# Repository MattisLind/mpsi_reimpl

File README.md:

# MPSI Rev2

A new HP 9830 interface based on
[Brent Hilpert's MPSI](https://madrona.ca/e/HP9830/mpsi/index.html): a 5 V ATF1504AS
CPLD handles the bus, and an STM32F103CB serves files from a microSD card.
Two 74HCT165s capture input, separate SPI buses serve the HP link and SD,
and an SSD1306 OLED with up/down/select buttons controls operation.

MPSI Server handles paper tape, printer capture and Fast Mode cassette emulation.
Tape Controller uses an HP-resident MTAPE proxy to read/write the physical drive.
USB MSC takes exclusive ownership of SD and releases every HP output.
See [the tape analysis](requirements/07_tape_analysis.md).

The current draft includes:

- [VHDL RTL, handshake bench and container build flow](hardware/rev2/README.md).
- [STM32/CPLD package pins and tentative placement](requirements/08_pin_mapping.md).
- [Three-sheet KiCad schematic and unrouted placement](hardware/rev2/kicad/README.md),
  with the existing HP connector, USB-C protection and PA9/PA10 debug header.
- [Portable C firmware core](firmware/rev2/README.md).

Start with [requirements](requirements/README.md) and [open issues](open_issues.md).

```sh
make test
```

Requires make, a C11 compiler and either GHDL or the documented Docker image.
Tests cover bus handshakes, five interrupt choices, GP-only Controller decoding,
direct configuration updates, unbuffered data, CS-clocked flags, input capture, tape commands
and exclusive SD/MSC ownership.

The simplified ATF1504 design fits and generates JEDEC with all 29 requested pins,
JTAG and fourteen open-collector HP outputs. RTL and fitter-emitted functional
equations each pass 2,000 checks at 9, 18 and 24 MHz SPI. These are zero-delay
tests; the F103 is specified up to 18 MHz, and 9 MHz is the provisional board rate.
This remains a design draft. Timing, fitter-report accounting, electrical current/rail and power-up validation, PCB routing,
and Arduino SD/USB/UI/Controller drivers also remain open. The STM32 pin map uses
PB14/PB10 as direct 5 V tolerant inputs, subject to supply/reset constraints.

Previous files remain in `MPSIBOARD`, `hardware/pld` and `software`.
The original README is preserved in [docs/legacy_design.md](docs/legacy_design.md).

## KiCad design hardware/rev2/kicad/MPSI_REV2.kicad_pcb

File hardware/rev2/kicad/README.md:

# KiCad draft

Open [MPSI_REV2.kicad_pro](MPSI_REV2.kicad_pro) in KiCad 10.

The root sheet contains the copied HP connector, ATF1504AS-10JU44, two 74HCT165s,
JTAG and reset/control pulls. The MCU sheet contains STM32F103CBT6, microSD with
card detection, OLED/buttons, USART1 debug, SWD, boot jumper and 8 MHz crystal.
The USB/power sheet copies the paper-tape project's USB-C/USBLC6 circuit and
Schottky source isolation, with TLV75533 3.3 V regulation.

The 64-footprint board is an **unrouted placement draft**. Its HP connector and
Edge.Cuts use the current legacy board. All fifty connector pad positions,
sizes, angles and layers are checked against that board when regenerated.
The CPLD and HCT165s sit beside the HP edge connector; MCU is to their right,
with SD/UI/debug/USB towards the other edges. Mechanical fit and routing remain
to be reviewed. The simplified CPLD fits with the requested package pins, including
CS moved to GCLK3 pin 41. COMMIT/overrun wiring is removed; PB0/PB11 and CPLD
34/39/40 are spare. Electrical/timing validation and routing remain open.

The project embeds symbols and supplies portable `Rev2.kicad_sym` and
`Rev2.pretty` libraries. The connector library is extracted from
`MPSIBOARD/MPSIBOARD.kicad_pcb`; board-file pad angles are normalized to library
angles without changing pad geometry. USB-C symbol/footprint and circuit values
come from [the paper-tape project](https://github.com/MattisLind/hp21xx_papertape_emulator/tree/06787ada3dd411305c0451a057edc152249f1b82/kicad/hp21xx_papertape_emulator).
Original projects are untouched.

The schematic generator uses installed KiCad symbol libraries and local copies
of that reference schematic/PCB. Its `--reference`, `--reference-pcb` and
`--symbols` arguments allow overriding the defaults. The saved KiCad project
does not depend on those source files being installed.

```sh
python3 scripts/generate_rev2_schematic.py
kicad-cli sch export netlist --output /tmp/mpsi-rev2.net hardware/rev2/kicad/MPSI_REV2.kicad_sch
python3 scripts/check_rev2_pins.py --netlist /tmp/mpsi-rev2.net
```

For the placement generator use KiCad's bundled Python with its `pcbnew` module;
it consumes the above netlist, including explicit unconnected pin nets. On macOS:

```sh
/Applications/KiCad/KiCad.app/Contents/Frameworks/Python.framework/Versions/3.9/bin/python3.9 scripts/generate_rev2_placement.py
```

`components.json` records the schematic components/UUID paths used by that
generator; `pinmap.json` in the parent directory is the package-pin contract.
Generators overwrite these draft files, so update generator source alongside
manual schematic changes if regeneration is needed.

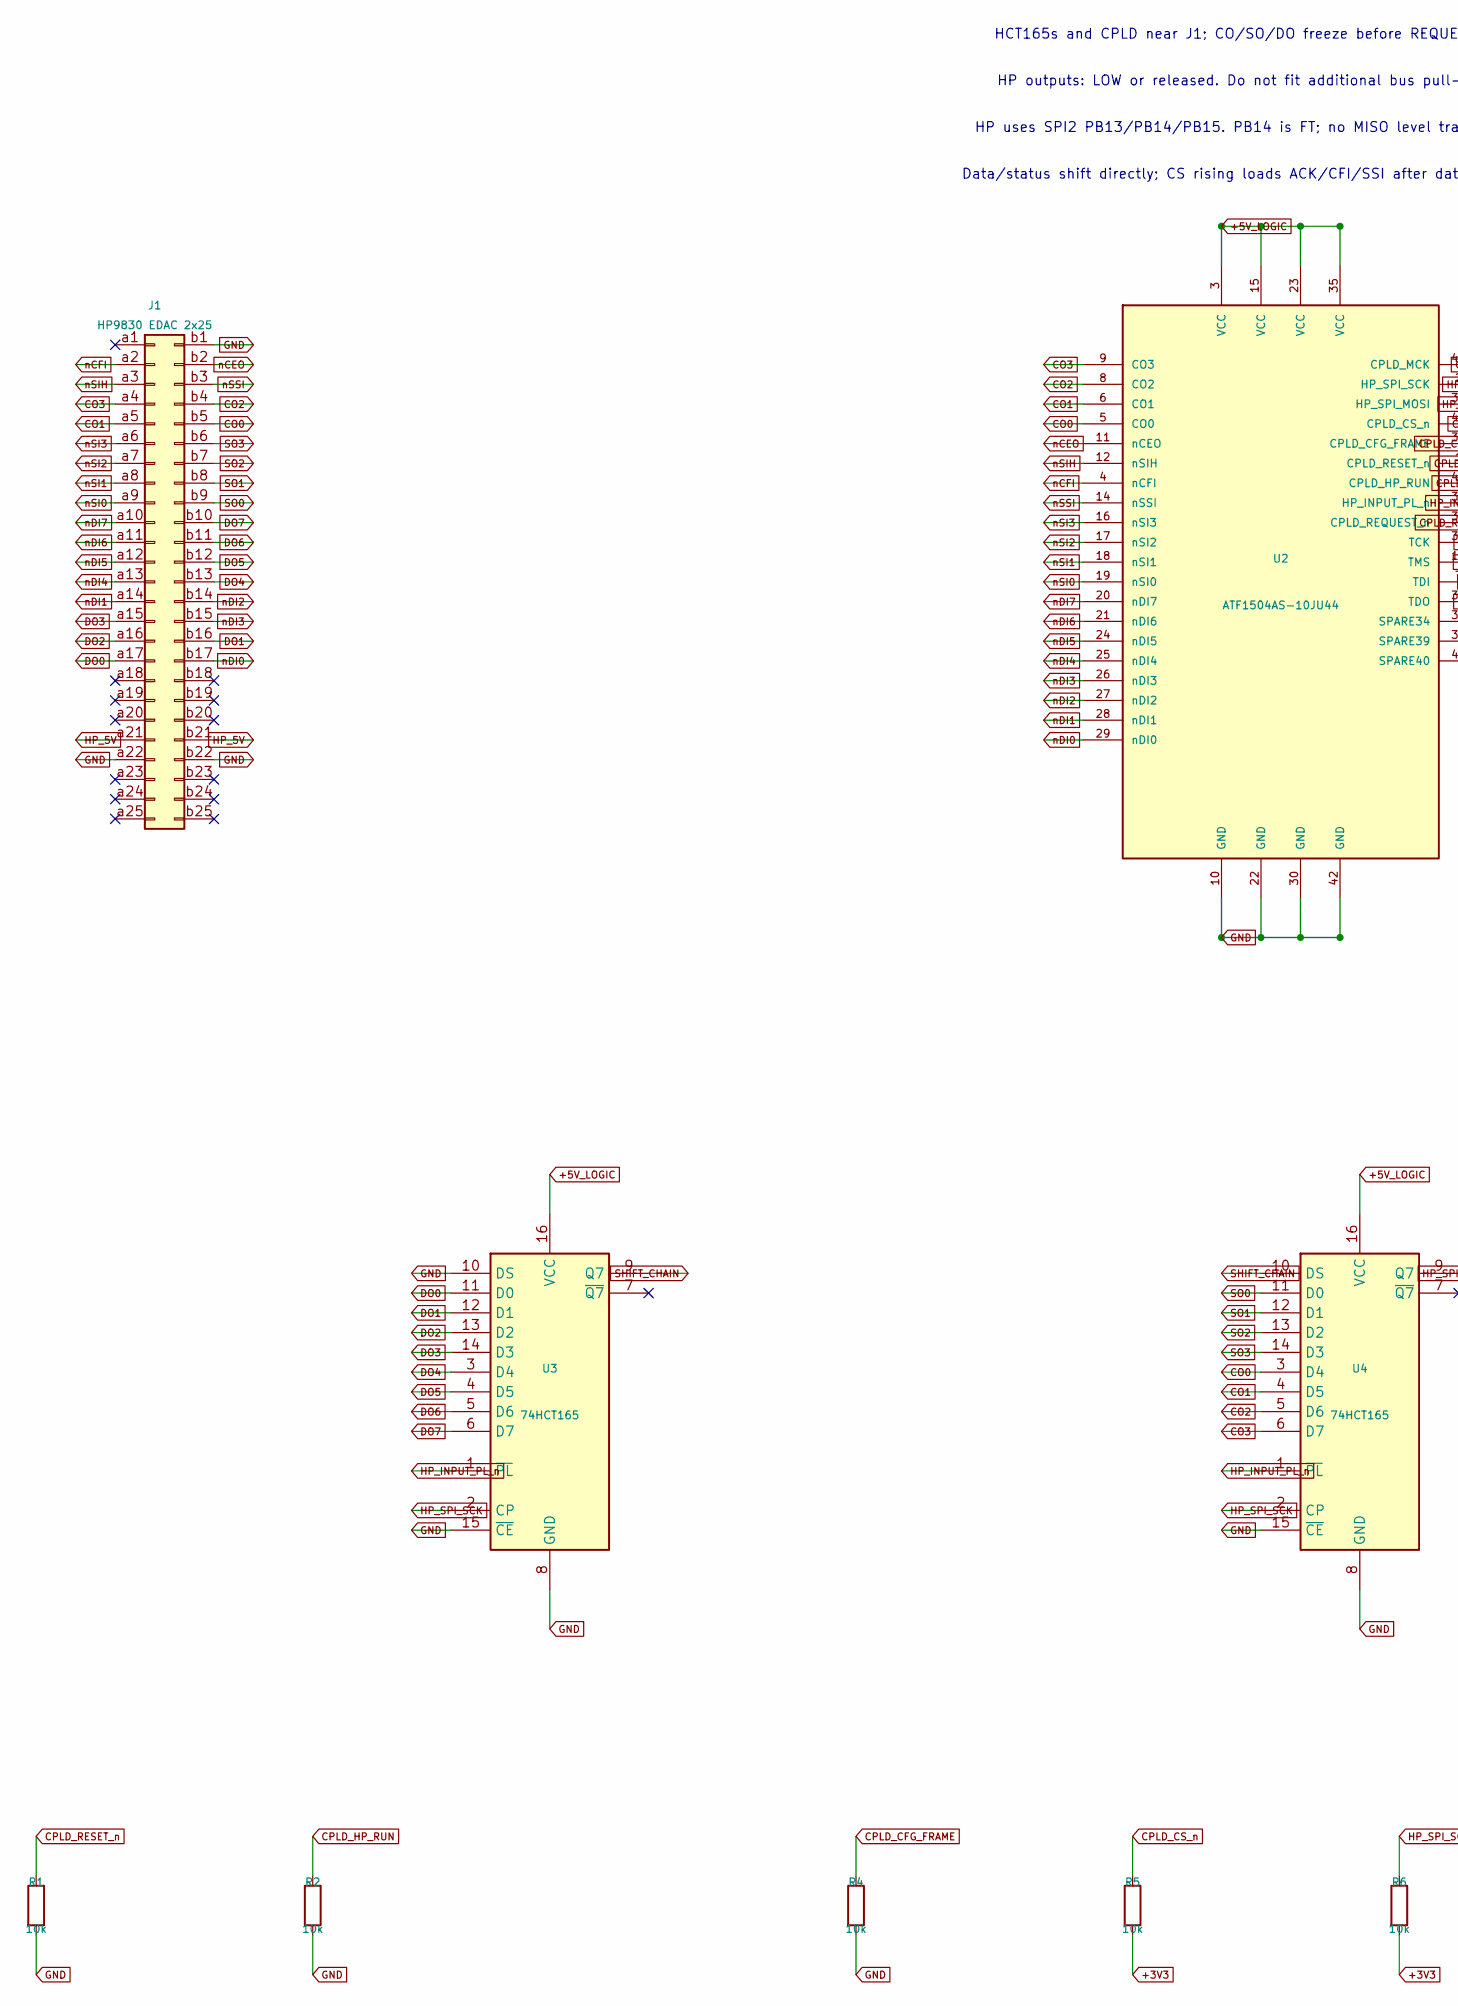
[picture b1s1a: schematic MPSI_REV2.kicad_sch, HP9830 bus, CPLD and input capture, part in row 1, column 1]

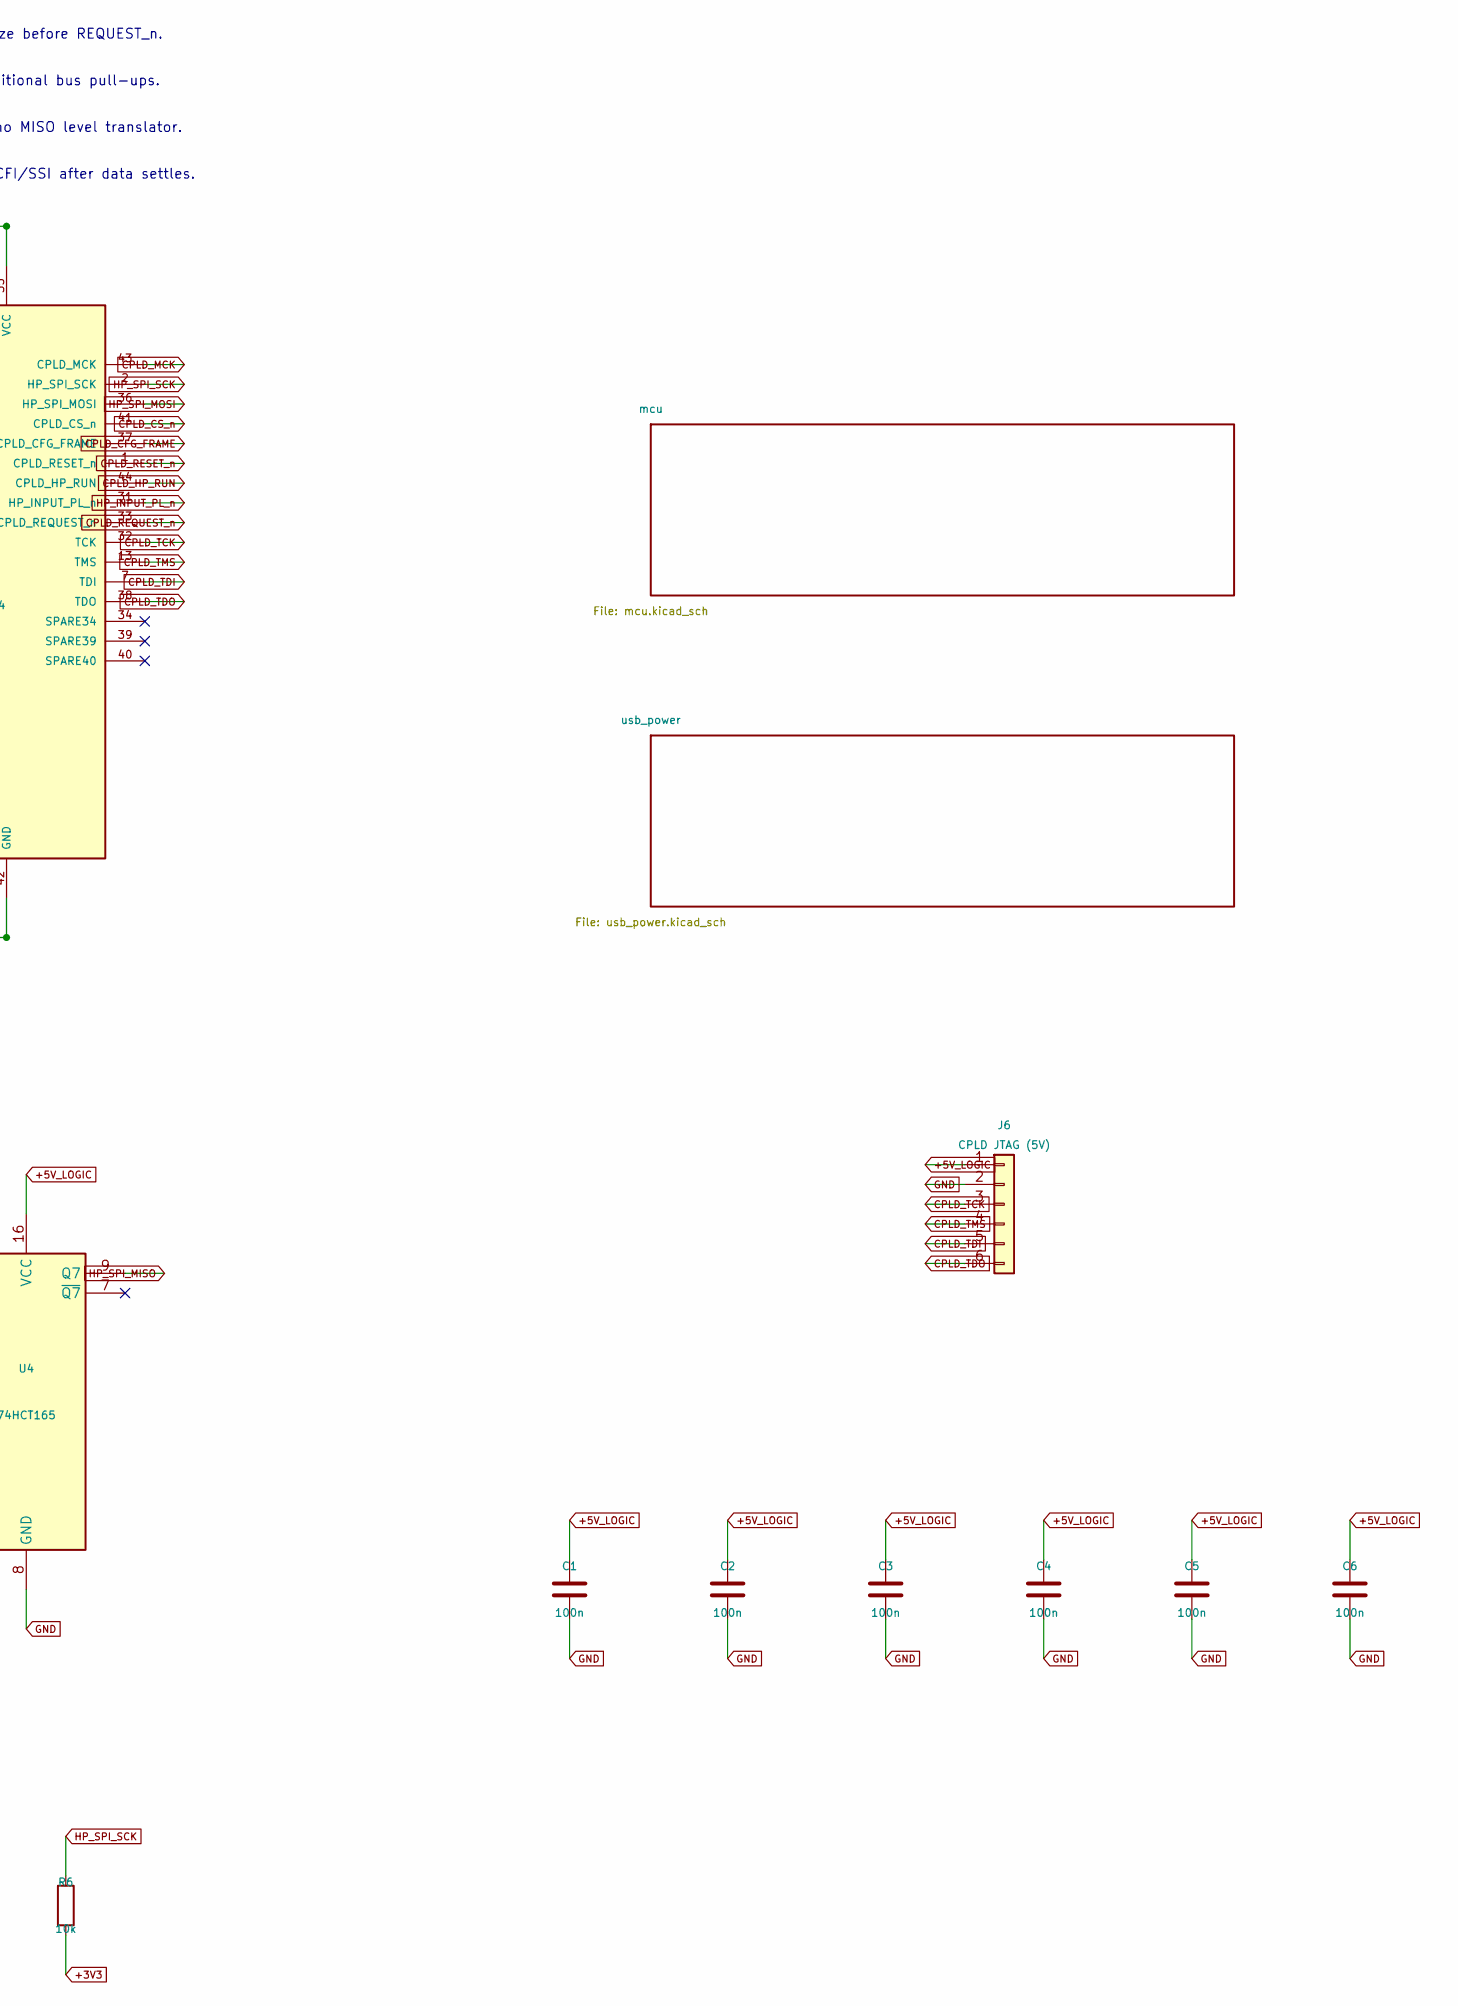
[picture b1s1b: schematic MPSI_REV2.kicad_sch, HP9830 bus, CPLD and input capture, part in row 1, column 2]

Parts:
C1, C2, C3, C4, C5, C6: 100n; C_0603_1608Metric
J1: HP9830 EDAC 2x25; HP9830_EDAC_2x25
J6: CPLD JTAG (5V); PinHeader_1x06_P2.54mm_Vertical
R1, R2, R4, R5, R6: 10k; R_0603_1608Metric
U2: ATF1504AS-10JU44; PLCC-44_16.6x16.6mm_P1.27mm
U3, U4: 74HCT165; SOIC-16_3.9x9.9mm_P1.27mm

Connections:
+3V3: R5.2, R6.2; also elsewhere on the board
+5V_LOGIC: C1.1, C2.1, C3.1, C4.1, C5.1, C6.1, J6.1, U2.3 (VCC), U2.15 (VCC), U2.23 (VCC), U2.35 (VCC), U3.16 (VCC), U4.16 (VCC); also elsewhere on the board
CO0: J1.b5, U2.5 (CO0), U4.3 (D4)
CO1: J1.a5, U2.6 (CO1), U4.4 (D5)
CO2: J1.b4, U2.8 (CO2), U4.5 (D6)
CO3: J1.a4, U2.9 (CO3), U4.6 (D7)
CPLD_CFG_FRAME: R4.1, U2.37 (CPLD_CFG_FRAME); also elsewhere on the board
CPLD_CS_n: R5.1, U2.41 (CPLD_CS_n); also elsewhere on the board
CPLD_HP_RUN: R2.1, U2.44 (CPLD_HP_RUN); also elsewhere on the board
CPLD_MCK: U2.43 (CPLD_MCK); also elsewhere on the board
CPLD_REQUEST_n: U2.33 (CPLD_REQUEST_n); also elsewhere on the board
CPLD_RESET_n: R1.1, U2.1 (CPLD_RESET_n); also elsewhere on the board
CPLD_TCK: J6.3, U2.32 (TCK)
CPLD_TDI: J6.5, U2.7 (TDI)
CPLD_TDO: J6.6, U2.38 (TDO)
CPLD_TMS: J6.4, U2.13 (TMS)
DO0: J1.a17, U3.11 (D0)
DO1: J1.b16, U3.12 (D1)
DO2: J1.a16, U3.13 (D2)
DO3: J1.a15, U3.14 (D3)
DO4: J1.b13, U3.3 (D4)
DO5: J1.b12, U3.4 (D5)
DO6: J1.b11, U3.5 (D6)
DO7: J1.b10, U3.6 (D7)
GND: C1.2, C2.2, C3.2, C4.2, C5.2, C6.2, J1.a22, J1.b1, J1.b22, J6.2, R1.2, R2.2, R4.2, U2.10 (GND), U2.22 (GND), U2.30 (GND), U2.42 (GND), U3.8 (GND), U3.10 (DS), U3.15 (~CE), U4.8 (GND), U4.15 (~CE); also elsewhere on the board
HP_5V: J1.a21, J1.b21; also elsewhere on the board
HP_INPUT_PL_n: U2.31 (HP_INPUT_PL_n), U3.1 (~PL), U4.1 (~PL)
HP_SPI_MISO: U4.9 (Q7); also elsewhere on the board
HP_SPI_MOSI: U2.36 (HP_SPI_MOSI); also elsewhere on the board
HP_SPI_SCK: R6.1, U2.2 (HP_SPI_SCK), U3.2 (CP), U4.2 (CP); also elsewhere on the board
SHIFT_CHAIN: U3.9 (Q7), U4.10 (DS)
SO0: J1.b9, U4.11 (D0)
SO1: J1.b8, U4.12 (D1)
SO2: J1.b7, U4.13 (D2)
SO3: J1.b6, U4.14 (D3)
nCEO: J1.b2, U2.11 (nCEO)
nCFI: J1.a2, U2.4 (nCFI)
nDI0: J1.b17, U2.29 (nDI0)
nDI1: J1.a14, U2.28 (nDI1)
nDI2: J1.b14, U2.27 (nDI2)
nDI3: J1.b15, U2.26 (nDI3)
nDI4: J1.a13, U2.25 (nDI4)
nDI5: J1.a12, U2.24 (nDI5)
nDI6: J1.a11, U2.21 (nDI6)
nDI7: J1.a10, U2.20 (nDI7)
nSI0: J1.a9, U2.19 (nSI0)
nSI1: J1.a8, U2.18 (nSI1)
nSI2: J1.a7, U2.17 (nSI2)
nSI3: J1.a6, U2.16 (nSI3)
nSIH: J1.a3, U2.12 (nSIH)
nSSI: J1.b3, U2.14 (nSSI)

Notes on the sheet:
HCT165s and CPLD near J1; CO/SO/DO freeze before REQUEST_n.
HP outputs: LOW or released. Do not fit additional bus pull-ups.
HP uses SPI2 PB13/PB14/PB15. PB14 is FT; no MISO level translator.
Data/status shift directly; CS rising loads ACK/CFI/SSI after data settles.

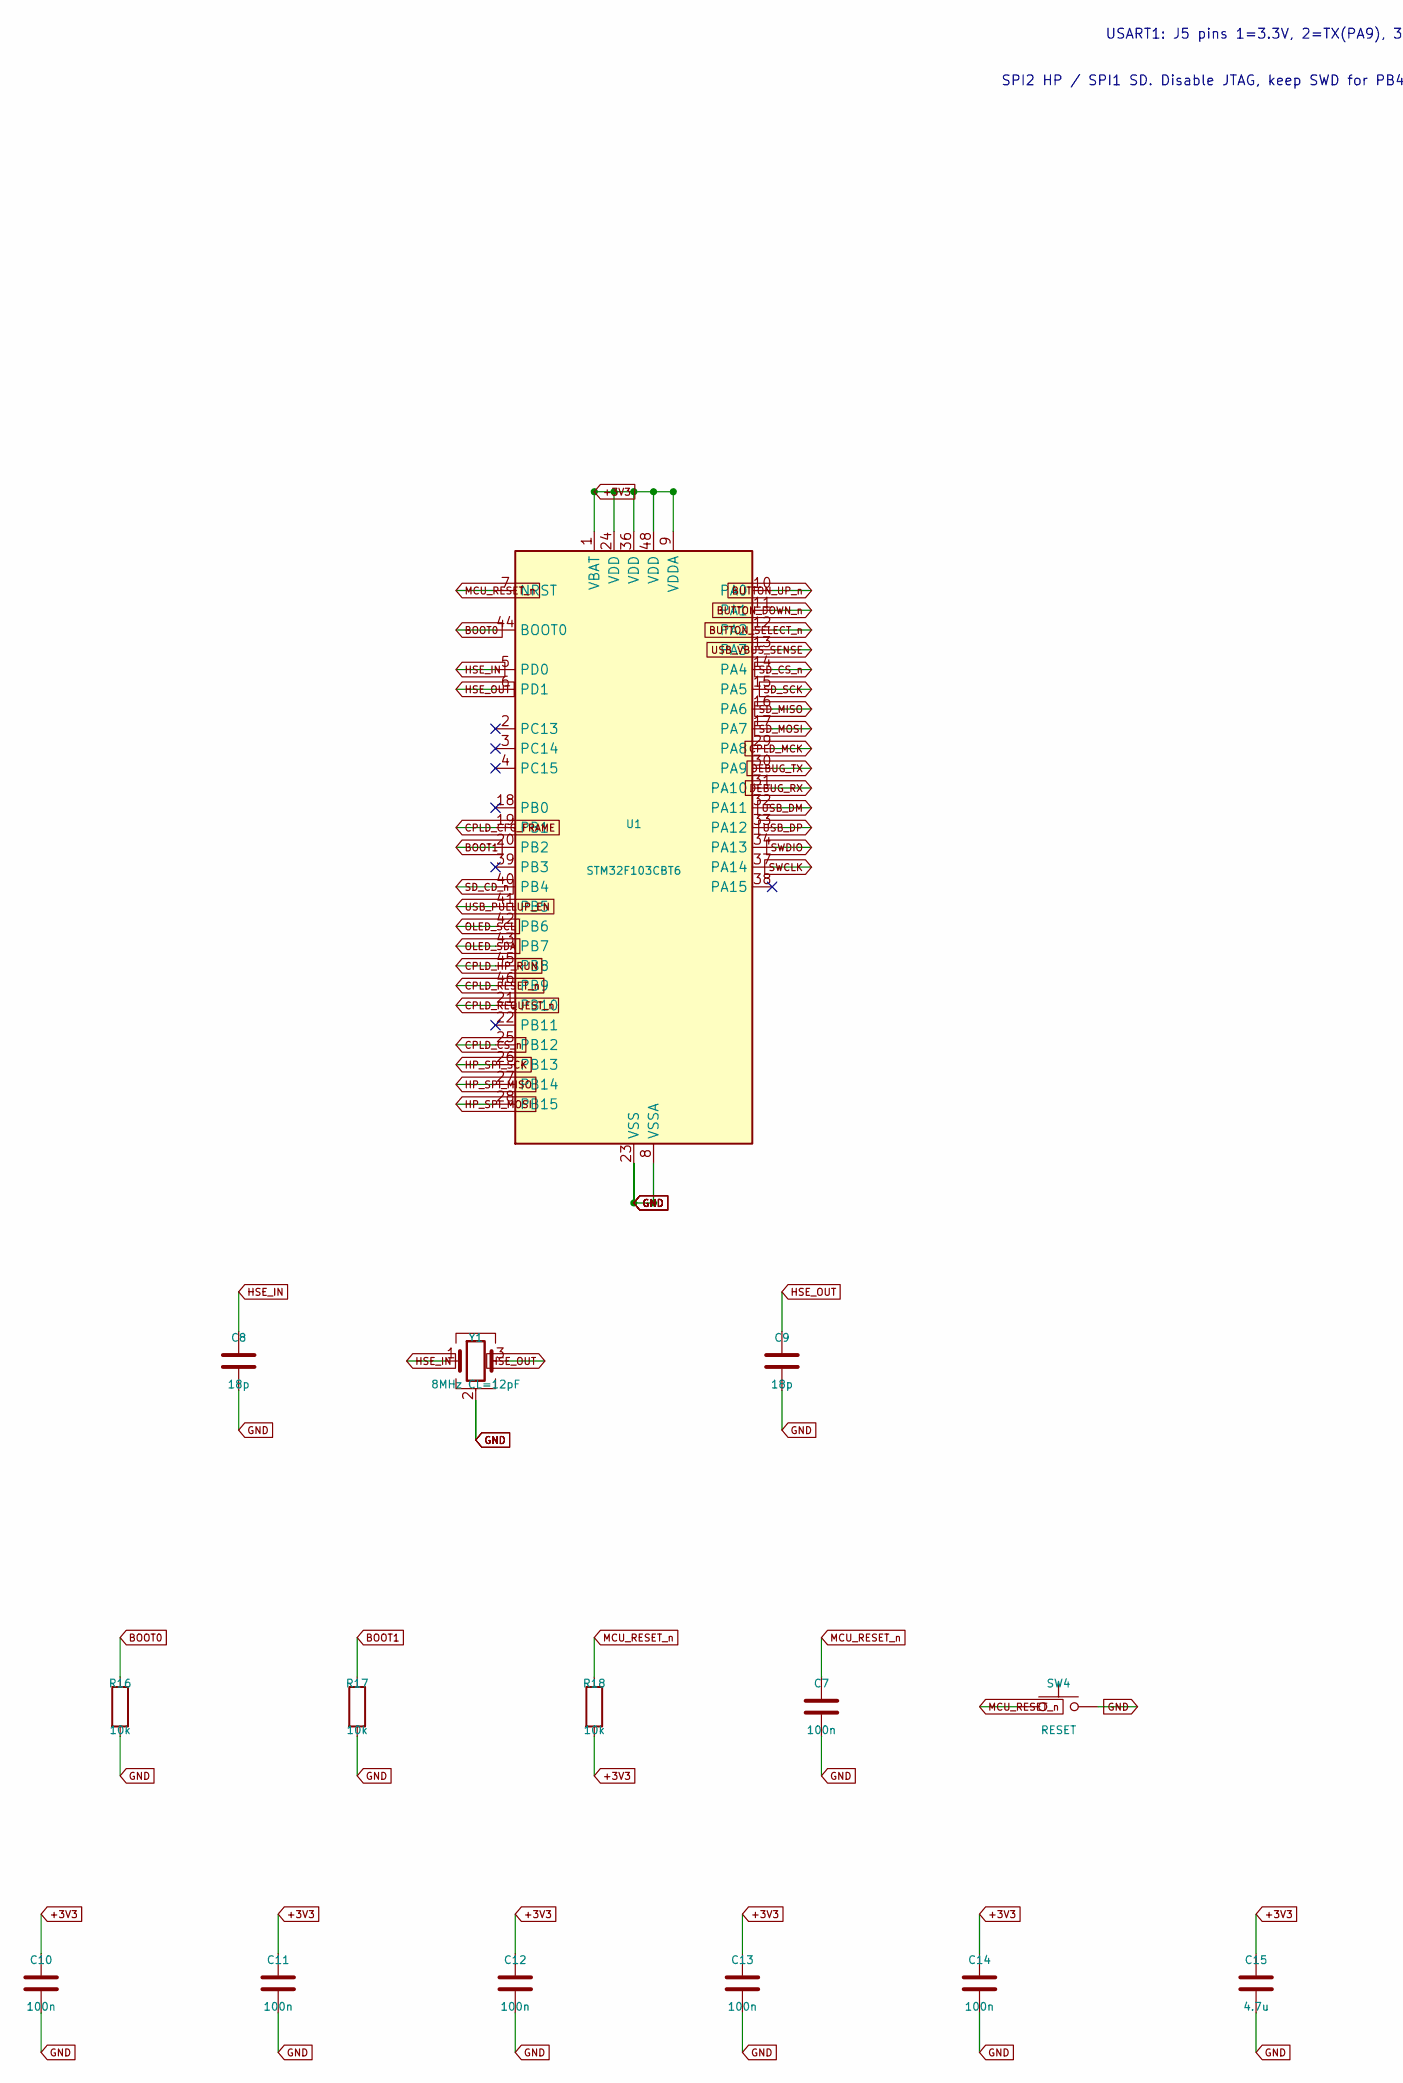
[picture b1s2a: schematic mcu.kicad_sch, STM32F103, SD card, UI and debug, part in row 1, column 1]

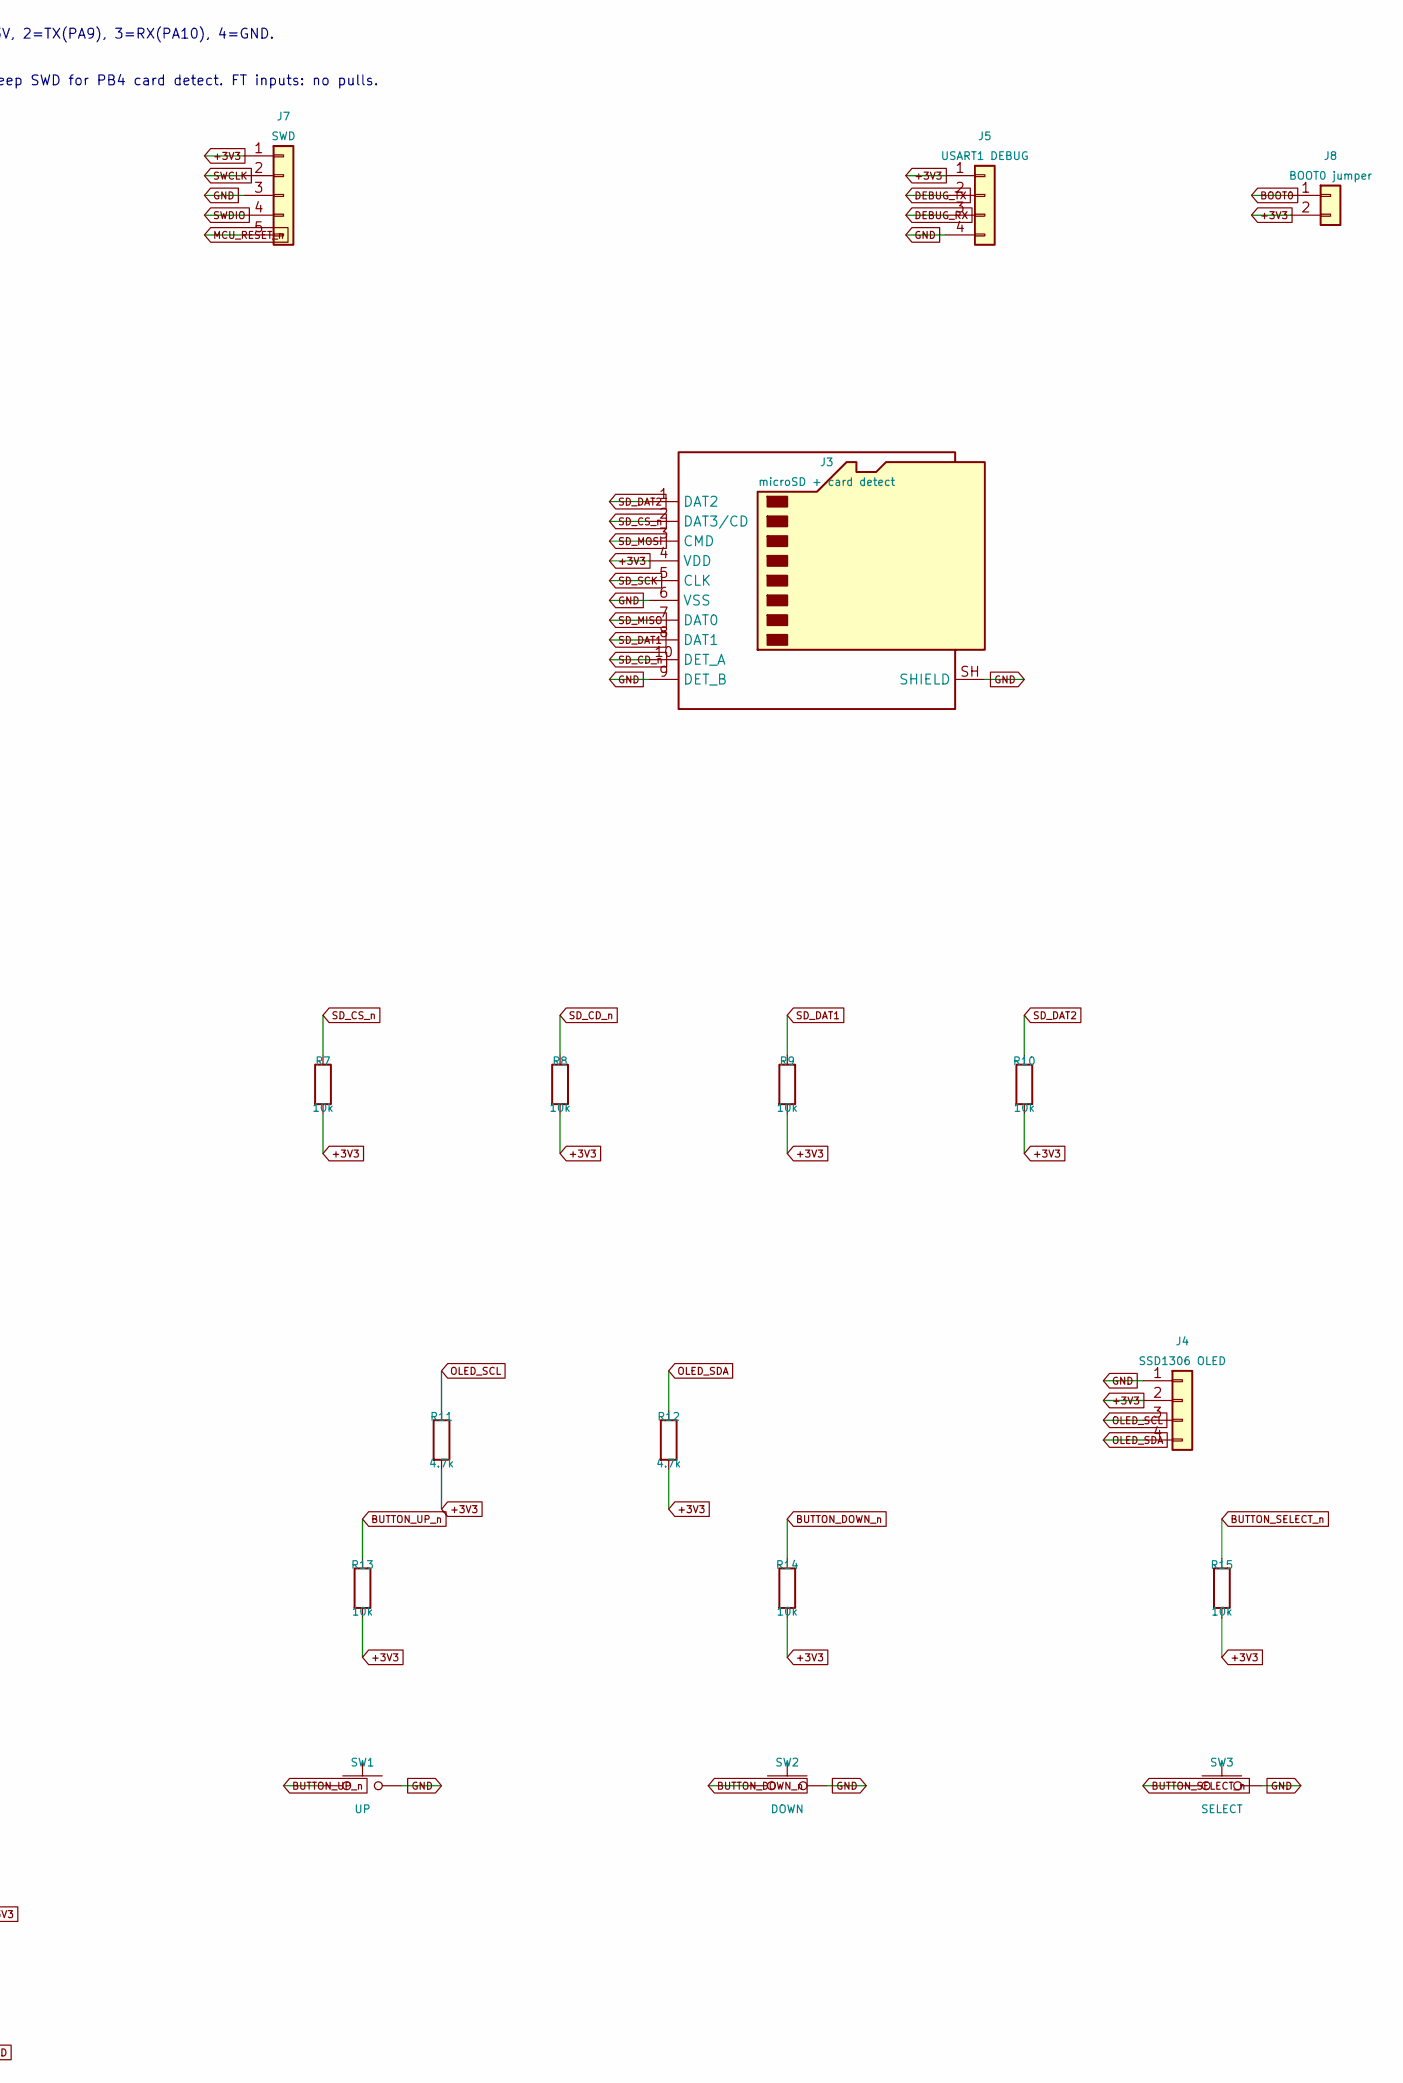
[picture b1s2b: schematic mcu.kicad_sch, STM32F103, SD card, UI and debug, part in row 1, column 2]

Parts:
C7, C10, C11, C12, C13, C14: 100n; C_0603_1608Metric
C8, C9: 18p; C_0603_1608Metric
C15: 4.7u; C_0603_1608Metric
J3: microSD + card detect; microSD_HC_Hirose_DM3AT-SF-PEJM5
J4: SSD1306 OLED; PinHeader_1x04_P2.54mm_Vertical
J5: USART1 DEBUG; PinHeader_1x04_P2.54mm_Vertical
J7: SWD; PinHeader_1x05_P2.54mm_Vertical
J8: BOOT0 jumper; PinHeader_1x02_P2.54mm_Vertical
R7, R8, R9, R10, R13, R14, R15, R16, R17, R18: 10k; R_0603_1608Metric
R11, R12: 4.7k; R_0603_1608Metric
SW1: UP; SW_PUSH_6mm_H5mm
SW2: DOWN; SW_PUSH_6mm_H5mm
SW3: SELECT; SW_PUSH_6mm_H5mm
SW4: RESET; SW_PUSH_6mm_H5mm
U1: STM32F103CBT6; LQFP-48_7x7mm_P0.5mm
Y1: 8MHz CL=12pF; Crystal_SMD_3225-4Pin_3.2x2.5mm

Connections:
+3V3: C10.1, C11.1, C12.1, C13.1, C14.1, C15.1, J3.4 (VDD), J4.2, J5.1, J7.1, J8.2, R7.2, R8.2, R9.2, R10.2, R11.2, R12.2, R13.2, R14.2, R15.2, R18.2, U1.1 (VBAT), U1.9 (VDDA), U1.24 (VDD), U1.36 (VDD), U1.48 (VDD); also elsewhere on the board
BOOT0: J8.1, R16.1, U1.44 (BOOT0)
BOOT1: R17.1, U1.20 (PB2)
BUTTON_DOWN_n: R14.1, SW2.1, U1.11 (PA1)
BUTTON_SELECT_n: R15.1, SW3.1, U1.12 (PA2)
BUTTON_UP_n: R13.1, SW1.1, U1.10 (PA0)
CPLD_CFG_FRAME: U1.19 (PB1); also elsewhere on the board
CPLD_CS_n: U1.25 (PB12); also elsewhere on the board
CPLD_HP_RUN: U1.45 (PB8); also elsewhere on the board
CPLD_MCK: U1.29 (PA8); also elsewhere on the board
CPLD_REQUEST_n: U1.21 (PB10); also elsewhere on the board
CPLD_RESET_n: U1.46 (PB9); also elsewhere on the board
DEBUG_RX: J5.3, U1.31 (PA10)
DEBUG_TX: J5.2, U1.30 (PA9)
GND: C7.2, C8.2, C9.2, C10.2, C11.2, C12.2, C13.2, C14.2, C15.2, J3.6 (VSS), J3.9 (DET_B), J3.SH (SHIELD), J4.1, J5.4, J7.3, R16.2, R17.2, SW1.2, SW2.2, SW3.2, SW4.2, U1.8 (VSSA), U1.23 (VSS), U1.35 (VSS), U1.47 (VSS), Y1.2 (G), Y1.4 (G); also elsewhere on the board
HP_SPI_MISO: U1.27 (PB14); also elsewhere on the board
HP_SPI_MOSI: U1.28 (PB15); also elsewhere on the board
HP_SPI_SCK: U1.26 (PB13); also elsewhere on the board
HSE_IN: C8.1, U1.5 (PD0), Y1.1
HSE_OUT: C9.1, U1.6 (PD1), Y1.3
MCU_RESET_n: C7.1, J7.5, R18.1, SW4.1, U1.7 (NRST)
OLED_SCL: J4.3, R11.1, U1.42 (PB6)
OLED_SDA: J4.4, R12.1, U1.43 (PB7)
SD_CD_n: J3.10 (DET_A), R8.1, U1.40 (PB4)
SD_CS_n: J3.2 (DAT3/CD), R7.1, U1.14 (PA4)
SD_DAT1: J3.8 (DAT1), R9.1
SD_DAT2: J3.1 (DAT2), R10.1
SD_MISO: J3.7 (DAT0), U1.16 (PA6)
SD_MOSI: J3.3 (CMD), U1.17 (PA7)
SD_SCK: J3.5 (CLK), U1.15 (PA5)
SWCLK: J7.2, U1.37 (PA14)
SWDIO: J7.4, U1.34 (PA13)
USB_DM: U1.32 (PA11); also elsewhere on the board
USB_DP: U1.33 (PA12); also elsewhere on the board
USB_PULLUP_EN: U1.41 (PB5); also elsewhere on the board
USB_VBUS_SENSE: U1.13 (PA3); also elsewhere on the board

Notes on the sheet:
USART1: J5 pins 1=3.3V, 2=TX(PA9), 3=RX(PA10), 4=GND.
SPI2 HP / SPI1 SD. Disable JTAG, keep SWD for PB4 card detect. FT inputs: no pulls.

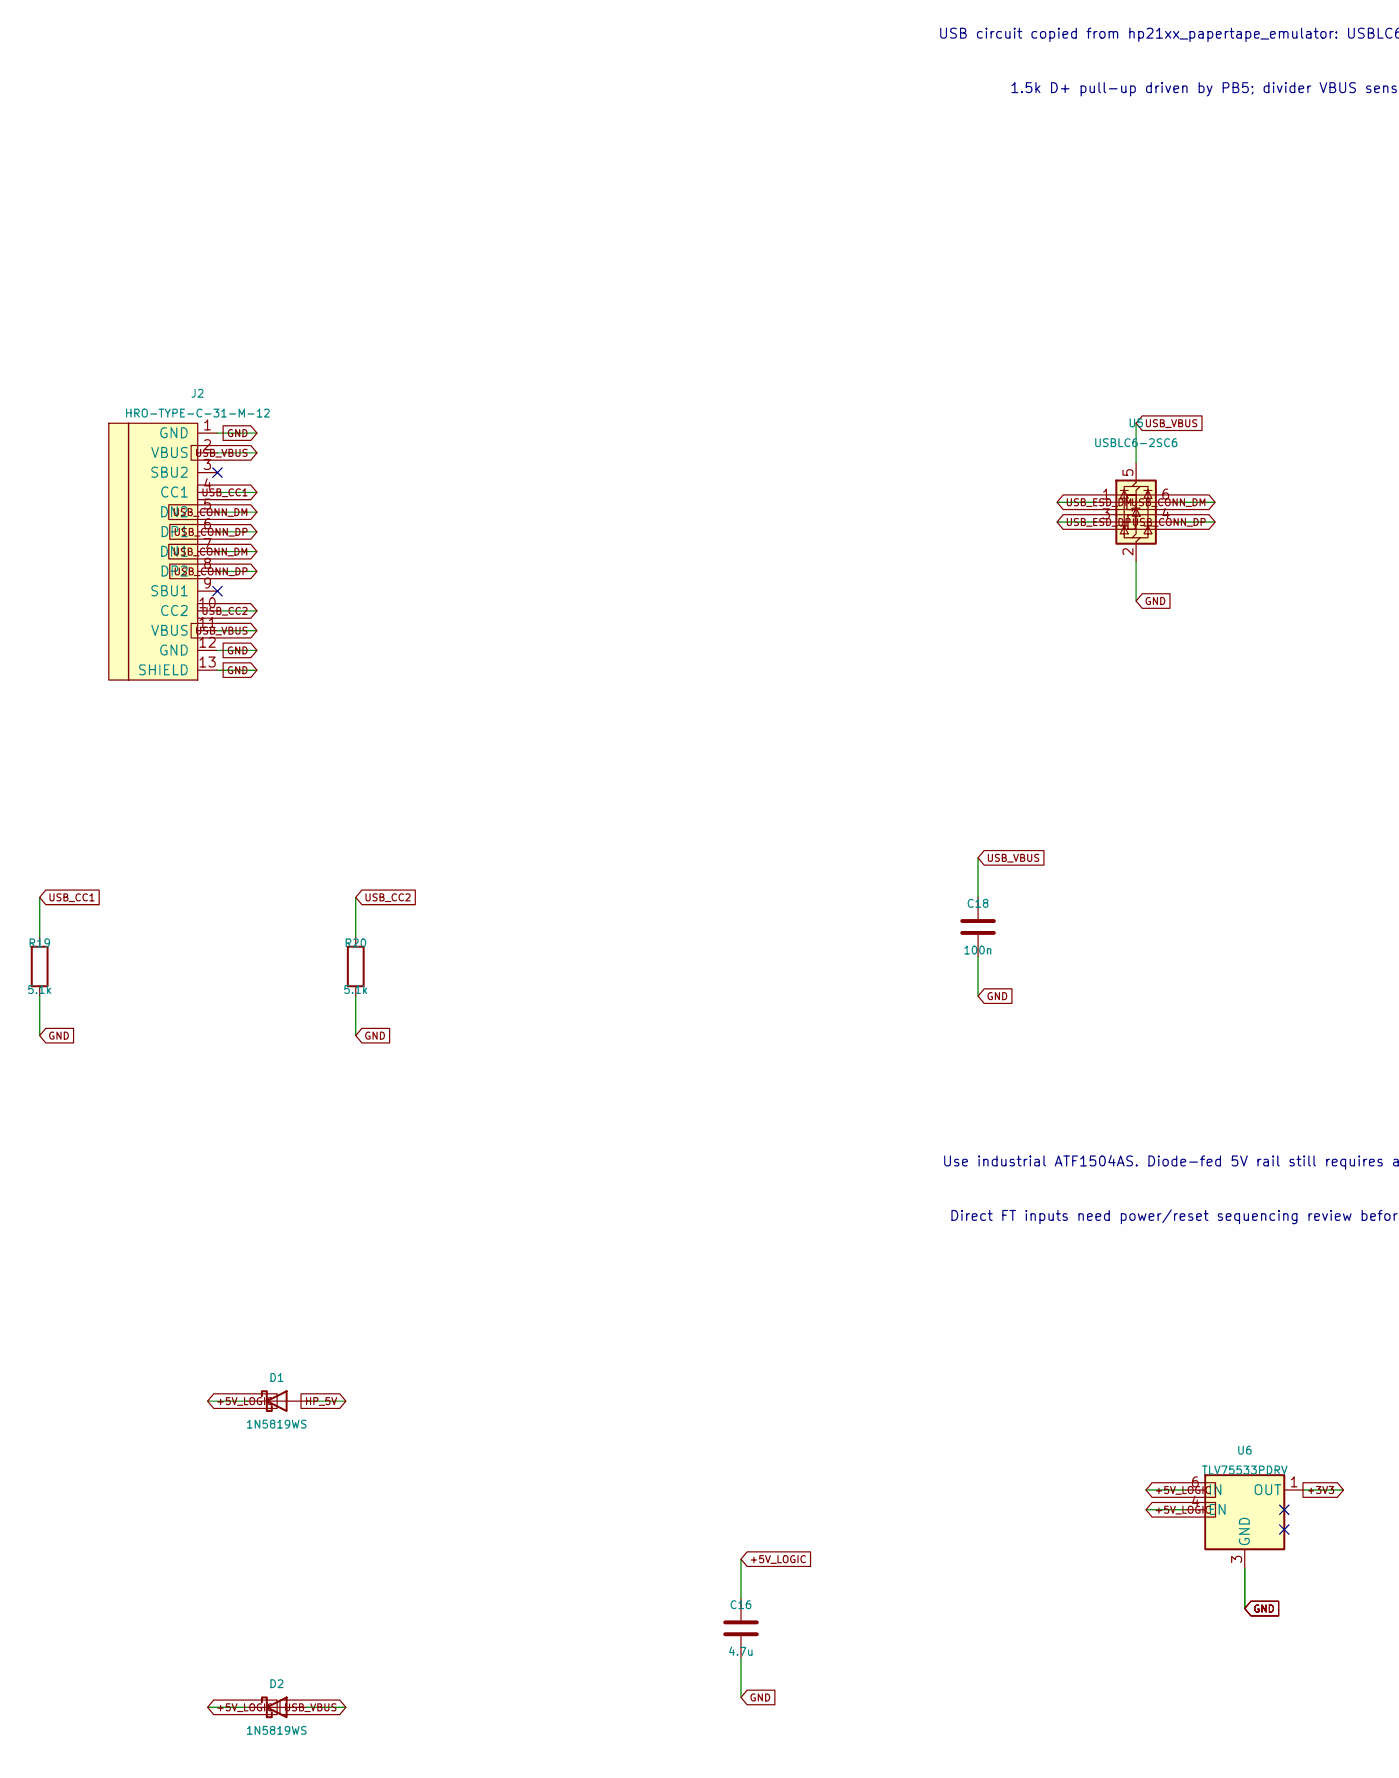
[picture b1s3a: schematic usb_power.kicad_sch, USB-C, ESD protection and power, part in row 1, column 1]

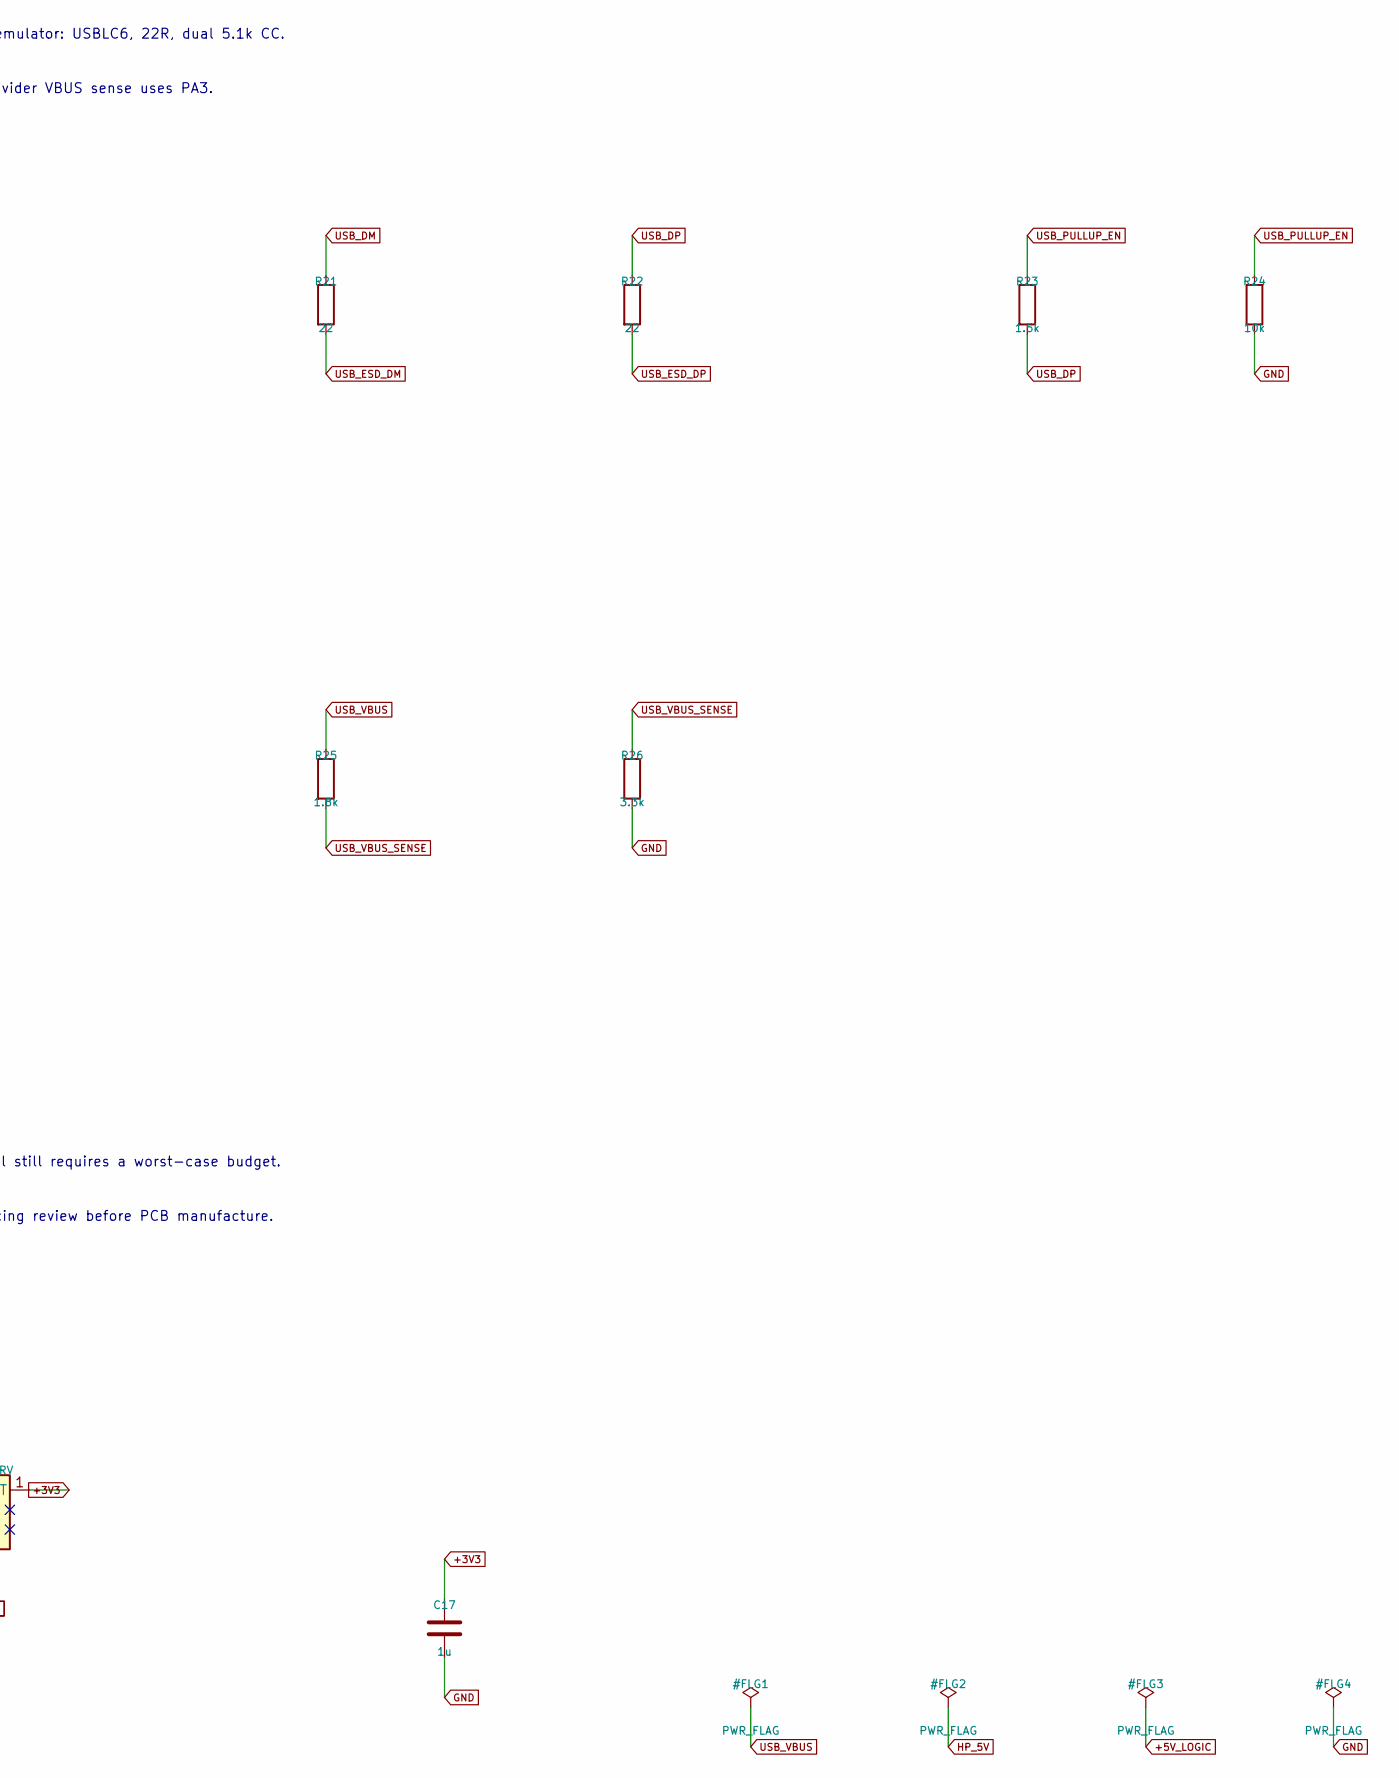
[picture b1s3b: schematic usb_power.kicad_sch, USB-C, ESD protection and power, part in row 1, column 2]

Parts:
C16: 4.7u; C_0603_1608Metric
C17: 1u; C_0603_1608Metric
C18: 100n; C_0603_1608Metric
D1, D2: 1N5819WS; D_SOD-323
J2: HRO-TYPE-C-31-M-12
R19, R20: 5.1k; R_0603_1608Metric
R21, R22: 22; R_0603_1608Metric
R23: 1.5k; R_0603_1608Metric
R24: 10k; R_0603_1608Metric
R25: 1.8k; R_0603_1608Metric
R26: 3.3k; R_0603_1608Metric
U5: USBLC6-2SC6; SOT-23-6
U6: TLV75533PDRV; WSON-6-1EP_2x2mm_P0.65mm_EP1x1.6mm

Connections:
+3V3: C17.1, U6.1 (OUT); also elsewhere on the board
+5V_LOGIC: C16.1, D1.1 (K), D2.1 (K), U6.4 (EN), U6.6 (IN); also elsewhere on the board
GND: C16.2, C17.2, C18.2, J2.1 (GND), J2.12 (GND), J2.13 (SHIELD), R19.2, R20.2, R24.2, R26.2, U5.2 (GND), U6.3 (GND), U6.7 (GND); also elsewhere on the board
HP_5V: D1.2 (A); also elsewhere on the board
USB_CC1: J2.4 (CC1), R19.1
USB_CC2: J2.10 (CC2), R20.1
USB_CONN_DM: J2.5 (DN2), J2.7 (DN1), U5.6 (I/O1)
USB_CONN_DP: J2.6 (DP1), J2.8 (DP2), U5.4 (I/O2)
USB_DM: R21.1; also elsewhere on the board
USB_DP: R22.1, R23.2; also elsewhere on the board
USB_ESD_DM: R21.2, U5.1 (I/O1)
USB_ESD_DP: R22.2, U5.3 (I/O2)
USB_PULLUP_EN: R23.1, R24.1; also elsewhere on the board
USB_VBUS: C18.1, D2.2 (A), J2.2 (VBUS), J2.11 (VBUS), R25.1, U5.5 (VBUS)
USB_VBUS_SENSE: R25.2, R26.1; also elsewhere on the board

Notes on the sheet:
USB circuit copied from hp21xx_papertape_emulator: USBLC6, 22R, dual 5.1k CC.
1.5k D+ pull-up driven by PB5; divider VBUS sense uses PA3.
Use industrial ATF1504AS. Diode-fed 5V rail still requires a worst-case budget.
Direct FT inputs need power/reset sequencing review before PCB manufacture.

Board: 2 copper layers, 64 parts (0 on the bottom side), 83 nets, no tracks yet.
